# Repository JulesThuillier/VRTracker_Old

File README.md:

# VR Tracker
VrTracker is an **Open Source position tracking device** to create great VR/AR experiences !
This system is **compatible with every kind of Virtual Reality headset**, like *Samsung Gear*, *Oculus Rift* or even *Google Cardboard* !

More informations here (check the Blog) : http://vrtracker.xyz/

All the code here is under GNU General Public License V3.0

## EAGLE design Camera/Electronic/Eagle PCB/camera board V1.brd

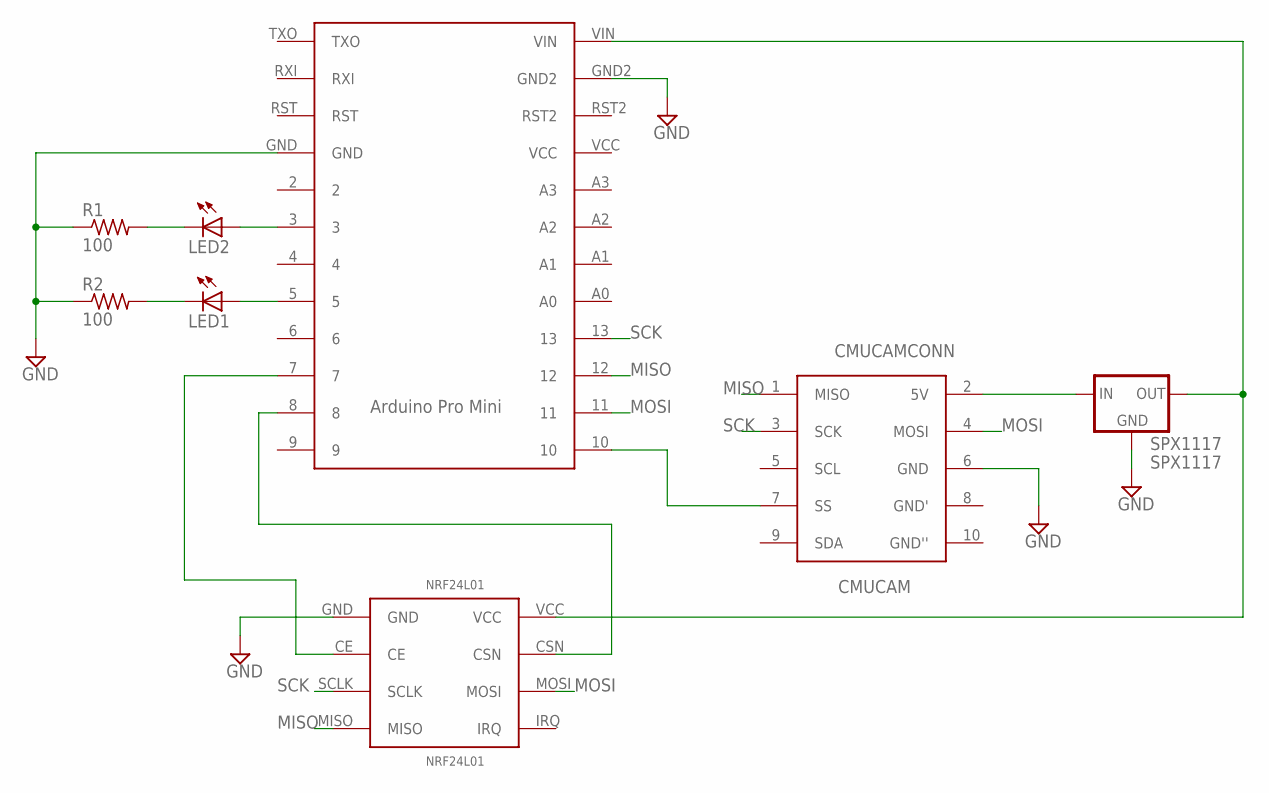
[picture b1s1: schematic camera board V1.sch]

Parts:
ARDUINOPROMINI: ARDUINOPROMINI
CMUCAM: CMUCAMCONN; DIP10
LED1, LED2: LED_E; LED_1206
NRF24L01: NRF24L01; DIP8
R1, R2: 100; M1206
SPX1117: SPX1117; SOT-223

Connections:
GND: ARDUINOPROMINI.GND, ARDUINOPROMINI.GND2, CMUCAM.6 (GND), NRF24L01.GND, R1.1, R2.1, SPX1117.1 (GND)
MISO: ARDUINOPROMINI.12, CMUCAM.1 (MISO), NRF24L01.MISO
MOSI: ARDUINOPROMINI.11, CMUCAM.4 (MOSI), NRF24L01.MOSI
unnamed: CMUCAM.2 (5V), SPX1117.3 (IN)
unnamed: ARDUINOPROMINI.VIN, NRF24L01.VCC, SPX1117.2 (OUT)
unnamed: ARDUINOPROMINI.8, NRF24L01.CSN
unnamed: ARDUINOPROMINI.7, NRF24L01.CE
unnamed: LED1.C, R2.2
unnamed: ARDUINOPROMINI.5, LED1.A
unnamed: ARDUINOPROMINI.10, CMUCAM.7 (SS)
unnamed: ARDUINOPROMINI.3, LED2.A
unnamed: LED2.C, R1.2
SCK: ARDUINOPROMINI.13, CMUCAM.3 (SCK), NRF24L01.SCLK

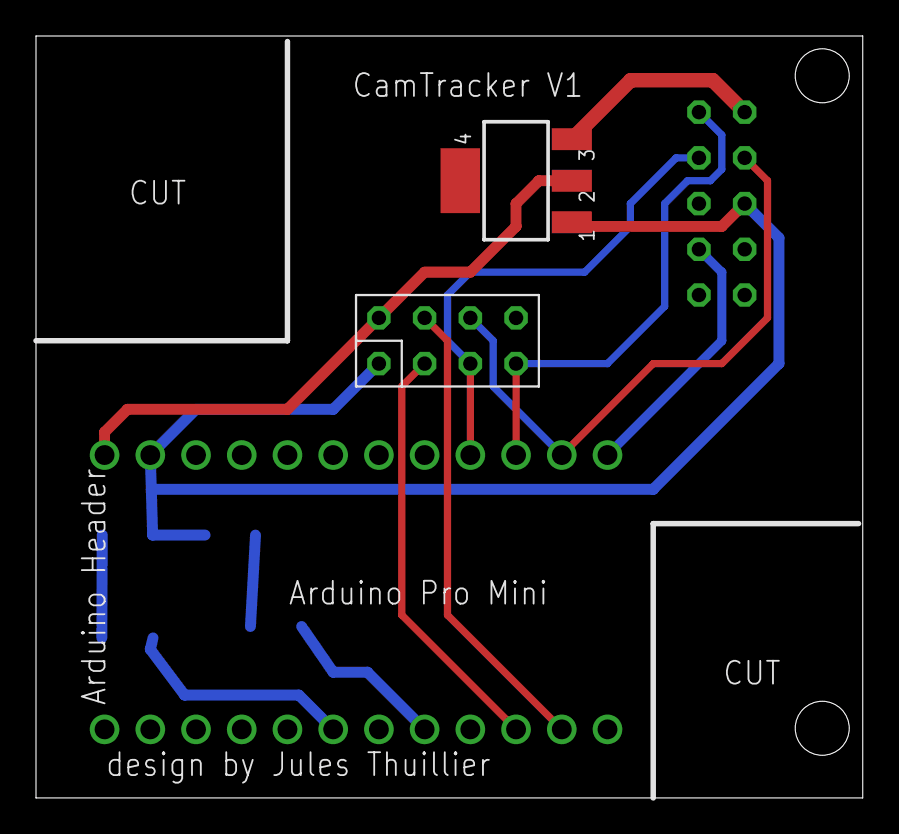
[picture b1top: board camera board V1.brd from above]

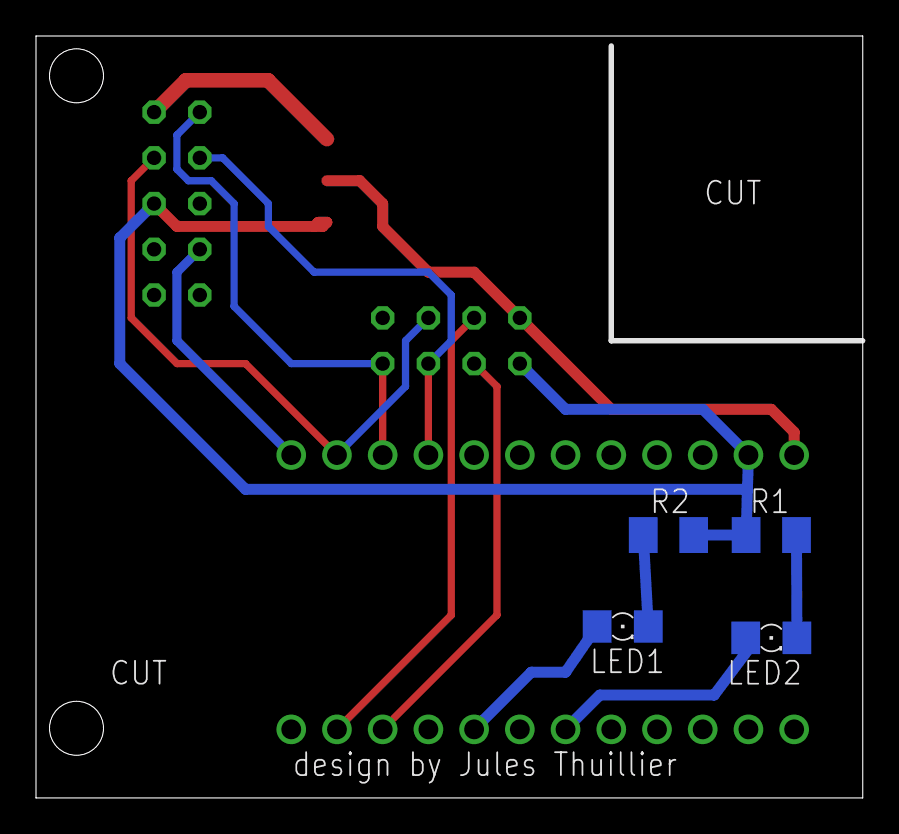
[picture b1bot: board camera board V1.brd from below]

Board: 2 copper layers, 45.9 x 42.3 mm, 8 parts (5 on the bottom side), 13 nets.

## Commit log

2015-08-19 Initial add RF24 lib
2015-08-19 moved rflib to base
2015-10-31 cleaning git
2015-10-31 Initial commit - camera only
2015-10-31 Added library for raspberry gateway
2015-12-11 up remove ds store
2015-12-20 added some files
2015-12-24 added PY
2015-12-24 added VrTracker Image
2015-12-27 nrf transmission in python OK
2015-12-27 old opencv tracking code added
2015-12-27 adding websocket opencv
2015-12-27 gateway nrf to websocket MVP OK
2015-12-28 Gateway NRF24 comm full Ok, parsing XY, Websocket OK. TODO : Calibration and 3D calculation
2016-01-07 Modifications brought to Gateway algo
2016-01-07 deleted old file
2016-01-07 added unity
2016-02-16 Huge cleany for new version
2016-02-16 Basic unity project
2016-03-10 added gateway fresh code
2016-03-10 added idea worspace for pycharm
2016-03-10 update camera websocket client instead of server
2016-03-11 correction workspace.xml
2016-03-11 workspace update
2016-03-13 gateway update architecture : 3D point, Observers for update, send back to user
2016-03-13 adding calibration methods
2016-03-14 Calibration sequence working, arduino code for tag (unfinished)
2016-03-14 Gateway tracking working but needs improvements
2016-03-14 bugfix
2016-03-15 tag and camera arduino code updated
2016-03-15 cleaning gateway
2016-03-15 adding #!/usr/bin/env python
2016-03-19 added debug, calibration html interface
2016-03-19 gateway corrections
2016-03-19 quickfix 3d positon websoicekr
2016-03-19 try to correct
2016-03-20 unity package added
2016-03-20 gitingore update
2016-03-20 improved New 2D Point handling (check in 3D Point observer)
2016-03-20 none
2016-03-20 correction calib interface
2016-03-20 correction, non functionnal
2016-03-20 test timestamp
2016-03-20 big update tracking alog lost point, new point
2016-03-20 cleaning unity
2016-03-20 ds store
2016-03-20 cleaning
2016-03-21 Unity package corrected to close Websocket on close app so gateway won't crash
2016-03-22 Correction/Update code Tag - Gateway Calibrate by camera (to test)
2016-03-23 Tag control and improved calibration
2016-03-24 Smooth added + corrections and avering
2016-03-24 corrections
2016-03-24 test debug gateway
2016-03-24 adding log point count
2016-03-24 debugging
2016-03-24 correction cam
2016-03-24 more debug
2016-03-24 forcing replace on new poitn (one player only)
2016-03-24 bugfix and testing
2016-03-24 tests
2016-03-24 calibration bugfix
2016-03-24 removing print to improve delay
2016-03-24 trying to avoid jittering - test
2016-03-24 remove print
2016-03-24 test
2016-03-31 added Android demo app
2016-04-05 calibration set tag on and off
2016-07-23 adding modified websocket library for python
2016-10-20 Removed for Copyright infrigment
2016-11-28 Backup pixy prototypes
